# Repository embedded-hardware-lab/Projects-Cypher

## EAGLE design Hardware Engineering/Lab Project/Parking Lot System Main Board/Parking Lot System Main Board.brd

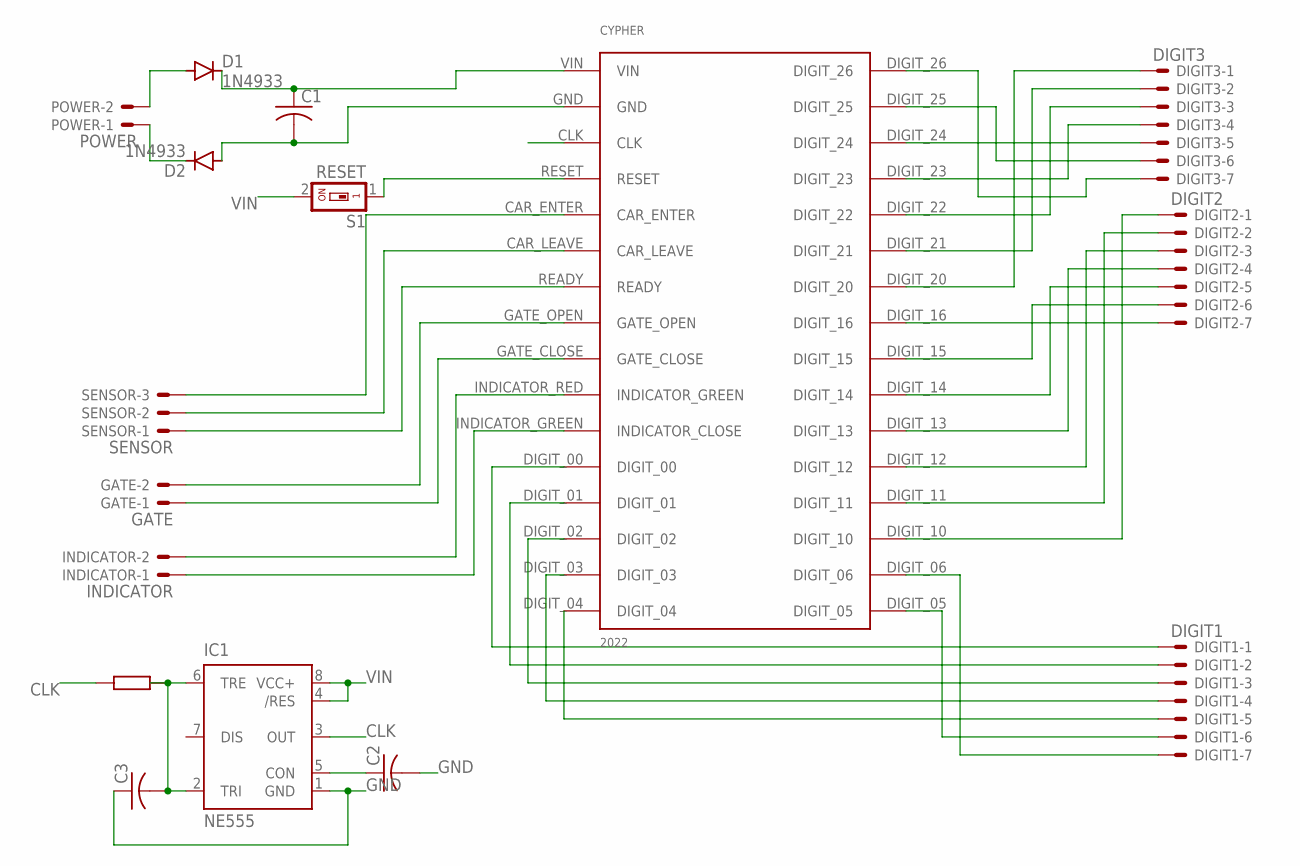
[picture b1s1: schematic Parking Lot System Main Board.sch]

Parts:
C1, C2, C3: C-US050-030X075; C050-030X075
CYPHER: CYPHER2022; CYPHER
D1, D2: 1N4933; DO41-10
DIGIT1: DIGIT1; 22-23-2071
DIGIT2: DIGIT2; 22-23-2071
DIGIT3: DIGIT3; 22-23-2071
GATE: GATE; 22-23-2021
IC1: NE555; DIL-08
INDICATOR: INDICATOR; 22-23-2021
POWER: POWER; 22-23-2021
S1: RESET; SMS-001
SENSOR: SENSOR; 22-23-2031

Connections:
CLK: CYPHER.CLK, IC1.3 (OUT); also elsewhere on the board
GND: C1.2, C2.2, C3.1, CYPHER.GND, D2.A, IC1.1 (GND); also elsewhere on the board
unnamed 2: CYPHER.CAR_ENTER, SENSOR.3; also elsewhere on the board
unnamed 3: CYPHER.RESET, S1.1; also elsewhere on the board
unnamed: D2.C, POWER.1
unnamed: D1.A, POWER.2
unnamed 6: CYPHER.CAR_LEAVE, SENSOR.2; also elsewhere on the board
unnamed 7: CYPHER.READY, SENSOR.1; also elsewhere on the board
unnamed: C3.2, IC1.2 (TRI), IC1.6 (TRE)
unnamed 9: CYPHER.GATE_OPEN, GATE.2; also elsewhere on the board
unnamed 10: CYPHER.GATE_CLOSE, GATE.1; also elsewhere on the board
unnamed 11: CYPHER.INDICATOR_RED (INDICATOR_GREEN), INDICATOR.2; also elsewhere on the board
unnamed: C2.1, IC1.5 (CON)
unnamed 13: CYPHER.INDICATOR_GREEN (INDICATOR_CLOSE), INDICATOR.1; also elsewhere on the board
unnamed 14: CYPHER.DIGIT_00, DIGIT1.1; also elsewhere on the board
unnamed 15: CYPHER.DIGIT_01, DIGIT1.2; also elsewhere on the board
unnamed 16: CYPHER.DIGIT_02, DIGIT1.3; also elsewhere on the board
unnamed 17: CYPHER.DIGIT_03, DIGIT1.4; also elsewhere on the board
unnamed 18: CYPHER.DIGIT_04, DIGIT1.5; also elsewhere on the board
unnamed 19: CYPHER.DIGIT_05, DIGIT1.6; also elsewhere on the board
unnamed 20: CYPHER.DIGIT_06, DIGIT1.7; also elsewhere on the board
unnamed 21: CYPHER.DIGIT_10, DIGIT2.1; also elsewhere on the board
unnamed 22: CYPHER.DIGIT_11, DIGIT2.2; also elsewhere on the board
unnamed 23: CYPHER.DIGIT_12, DIGIT2.3; also elsewhere on the board
unnamed 24: CYPHER.DIGIT_13, DIGIT2.4; also elsewhere on the board
unnamed 25: CYPHER.DIGIT_14, DIGIT2.5; also elsewhere on the board
unnamed 26: CYPHER.DIGIT_15, DIGIT2.6; also elsewhere on the board
unnamed 27: CYPHER.DIGIT_26, DIGIT3.7; also elsewhere on the board
unnamed 28: CYPHER.DIGIT_16, DIGIT2.7; also elsewhere on the board
unnamed 29: CYPHER.DIGIT_20, DIGIT3.1; also elsewhere on the board
unnamed 30: CYPHER.DIGIT_21, DIGIT3.2; also elsewhere on the board
unnamed 31: CYPHER.DIGIT_22, DIGIT3.3; also elsewhere on the board
unnamed 32: CYPHER.DIGIT_23, DIGIT3.4; also elsewhere on the board
unnamed 33: CYPHER.DIGIT_24, DIGIT3.5; also elsewhere on the board
unnamed 34: CYPHER.DIGIT_25, DIGIT3.6; also elsewhere on the board
VIN: C1.1, CYPHER.VIN, D1.C, IC1.4 (/RES), IC1.8 (VCC+), S1.2; also elsewhere on the board

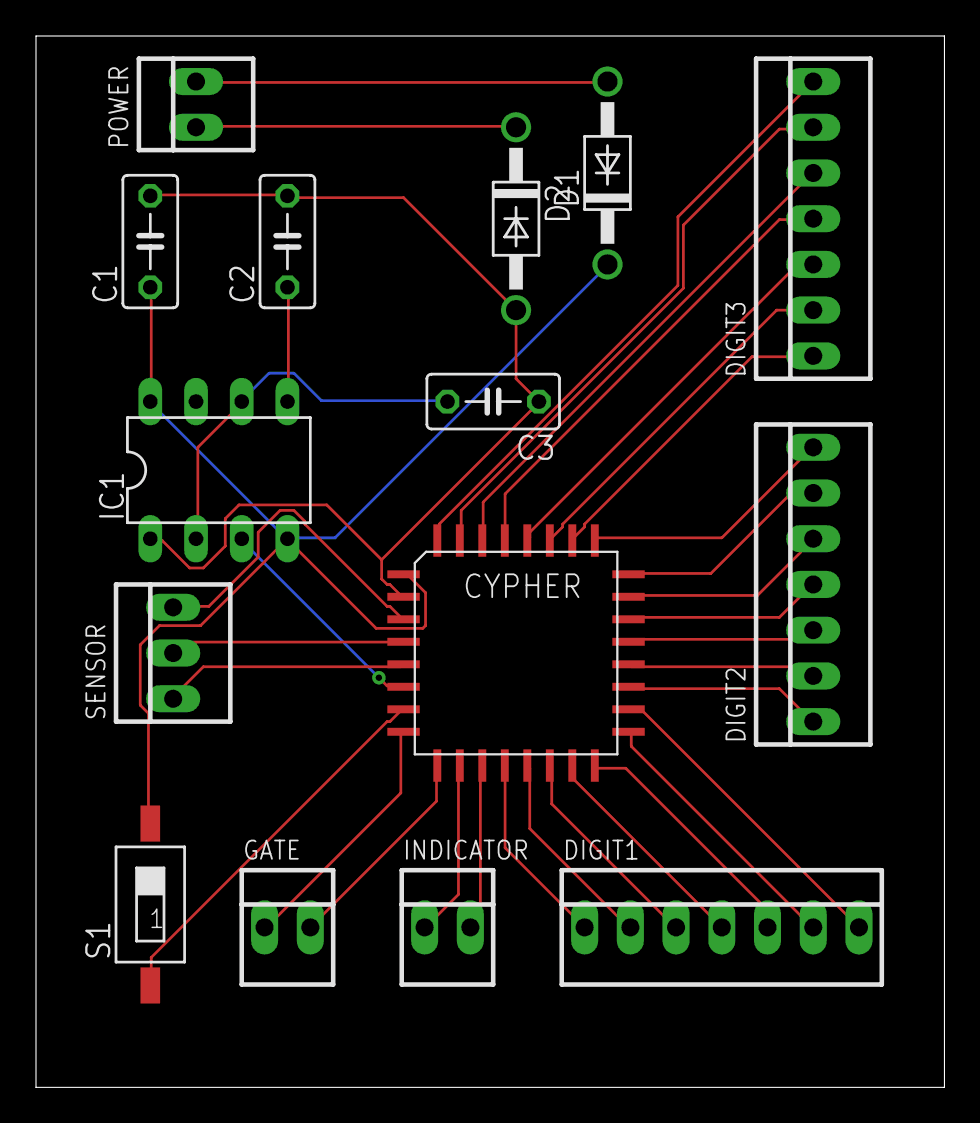
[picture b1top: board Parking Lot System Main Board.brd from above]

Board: 2 copper layers, 50.5 x 58.4 mm, 15 parts (0 on the bottom side), 36 nets.

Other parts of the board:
U$1: CYPHER2022; CYPHER

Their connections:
CLK: U$1.CLK; also elsewhere on the board
GND: U$1.GND; also elsewhere on the board
unnamed 2: U$1.CAR_ENTER; also elsewhere on the board
unnamed 3: U$1.RESET; also elsewhere on the board
unnamed 6: U$1.CAR_LEAVE; also elsewhere on the board
unnamed 7: U$1.READY; also elsewhere on the board
unnamed 9: U$1.GATE_OPEN; also elsewhere on the board
unnamed 10: U$1.GATE_CLOSE; also elsewhere on the board
unnamed 11: U$1.INDICATOR_RED; also elsewhere on the board
unnamed 13: U$1.INDICATOR_GREEN; also elsewhere on the board
unnamed 14: U$1.DIGIT_00; also elsewhere on the board
unnamed 15: U$1.DIGIT_01; also elsewhere on the board
unnamed 16: U$1.DIGIT_02; also elsewhere on the board
unnamed 17: U$1.DIGIT_03; also elsewhere on the board
unnamed 18: U$1.DIGIT_04; also elsewhere on the board
unnamed 19: U$1.DIGIT_05; also elsewhere on the board
unnamed 20: U$1.DIGIT_06; also elsewhere on the board
unnamed 21: U$1.DIGIT_10; also elsewhere on the board
unnamed 22: U$1.DIGIT_11; also elsewhere on the board
unnamed 23: U$1.DIGIT_12; also elsewhere on the board
unnamed 24: U$1.DIGIT_13; also elsewhere on the board
unnamed 25: U$1.DIGIT_14; also elsewhere on the board
unnamed 26: U$1.DIGIT_15; also elsewhere on the board
unnamed 27: U$1.DIGIT_26; also elsewhere on the board
unnamed 28: U$1.DIGIT_16; also elsewhere on the board
unnamed 29: U$1.DIGIT_20; also elsewhere on the board
unnamed 30: U$1.DIGIT_21; also elsewhere on the board
unnamed 31: U$1.DIGIT_22; also elsewhere on the board
unnamed 32: U$1.DIGIT_23; also elsewhere on the board
unnamed 33: U$1.DIGIT_24; also elsewhere on the board
unnamed 34: U$1.DIGIT_25; also elsewhere on the board
VIN: U$1.VIN; also elsewhere on the board

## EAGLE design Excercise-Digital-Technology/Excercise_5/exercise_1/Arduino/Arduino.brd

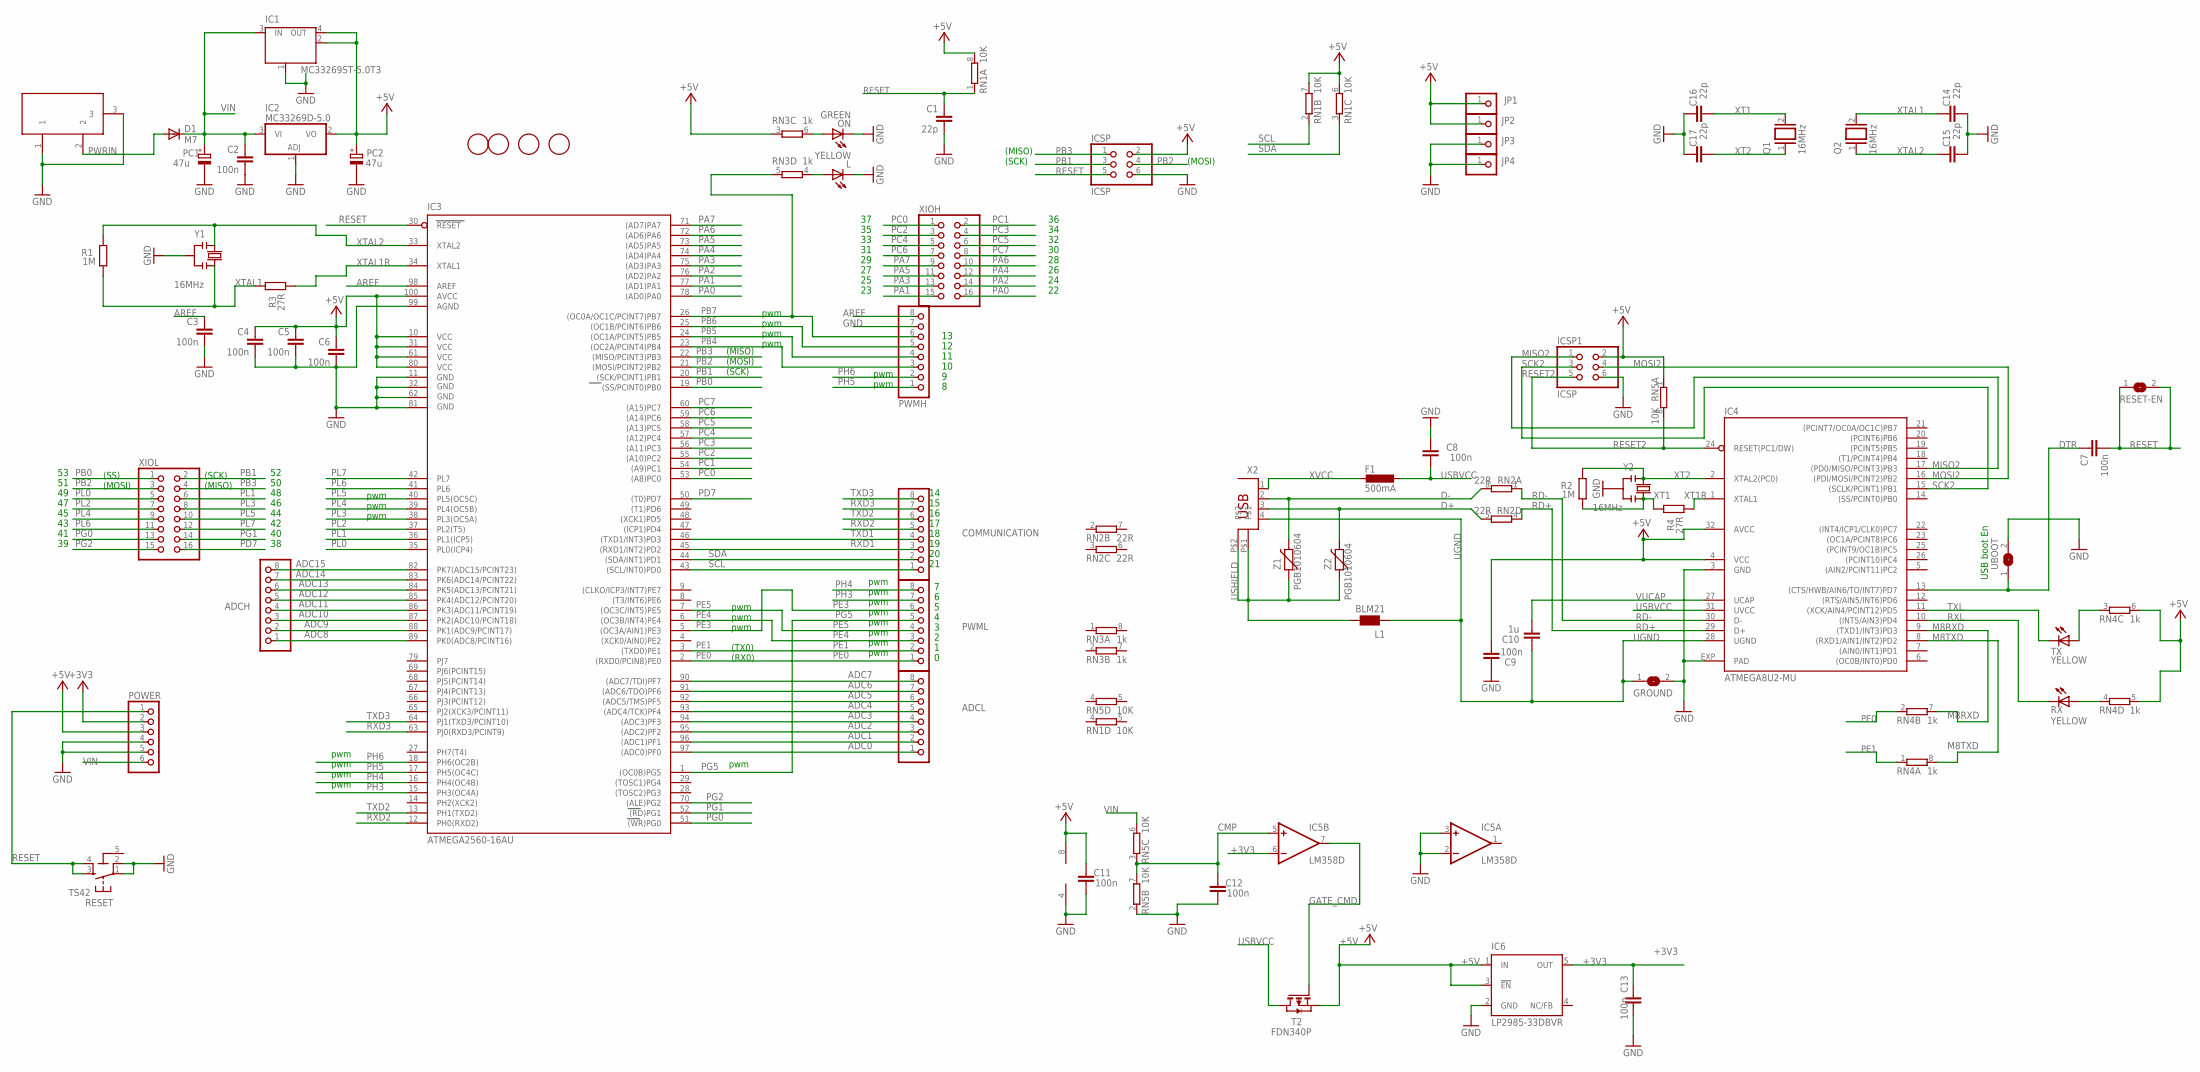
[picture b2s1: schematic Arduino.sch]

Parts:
ADCH: PINHD-1X8; 1X08
ADCL: PINHD-1X8; 1X08
C1, C14, C15, C16, C17: 22p; C0603-ROUND
C2, C3, C4, C5, C6, C7, C9, C12, C13: 100n; C0603-ROUND
C8, C11: 100n; C0603
C10: 1u; C0603-ROUND
COMMUNICATION: PINHD-1X8; 1X08
D1: M7; SMB
F1: 500mA; L1812
GROUND: SJ
IC1: MC33269ST-5.0T3; SOT223
IC2: MC33269D-5.0; DPACK
IC3: ATMEGA2560-16AU; TQFP100
IC4: ATMEGA8U2-MU; QFN32
IC5: LM358D; SO08
IC6: LP2985-33DBVR; SOT23-DBV
ICSP, ICSP1: ICSP; 2X03
JP1, JP2, JP3, JP4: PINHD-1X1; 1X01
L: YELLOW; CHIP-LED0805
L1: BLM21; 0805
ON: GREEN; CHIP-LED0805
PC1, PC2: 47u; PANASONIC_D
POWER: PINHD-1X6; 1X06
PWMH: PINHD-1X8; 1X08
PWML: PINHD-1X8; 1X08
Q1, Q2: 16MHz; QS
R1, R2: 1M; R0603-ROUND
R3, R4: 27R; R0603-ROUND
RESET: TS42
RESET-EN: SJ
RN1, RN5: 10K; CAT16
RN2: 22R; CAY16
RN3, RN4: 1k; CAY16
RX: YELLOW; CHIP-LED0805
T2: FDN340P; SOT-23
TX: YELLOW; CHIP-LED0805
U$2, U$3, U$4, U$5: FIDUCIALMOUNT; FIDUCIA-MOUNT
UBOOT: SJ
X1: DC21MMX; DC-21MM
X2: PN61729
XIOH: PINHD-2X8; 2X08
XIOL: PINHD-2X8; 2X08
Y1, Y2: 16MHz; RESONATOR
Z1, Z2: PGB1010604; CT/CN0603

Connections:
5-GND: RESET.5 (5-GND)
+3V3: C13.2, IC5.6 (-IN), IC6.5 (OUT), POWER.2
+5V: C4.1, C5.1, C6.1, C9.1, C11.2, IC1.2 (OUT), IC1.4 (OUT), IC2.2 (VO), IC3.10 (VCC), IC3.31 (VCC1), IC3.61 (VCC2), IC3.80 (VCC3), IC3.100 (AVCC), IC4.4 (VCC), IC4.32 (AVCC), IC5.8 (V+), IC6.1 (IN), IC6.3 (!EN), ICSP.2, ICSP1.2, JP1.1, JP2.1, PC2.+, POWER.3, RN1.6 (2), RN1.7 (2), RN1.8 (2), RN3.3 (1), RN4.5 (2), RN4.6 (2), RN5.1, T2.2 (S)
ADC0: ADCL.1, IC3.97 ((ADC0)PF0)
ADC1: ADCL.2, IC3.96 ((ADC1)PF1)
ADC2: ADCL.3, IC3.95 ((ADC2)PF2)
ADC3: ADCL.4, IC3.94 ((ADC3)PF3)
ADC4: ADCL.5, IC3.93 ((ADC4/TCK)PF4)
ADC5: ADCL.6, IC3.92 ((ADC5/TMS)PF5)
ADC6: ADCL.7, IC3.91 ((ADC6/TDO)PF6)
ADC7: ADCL.8, IC3.90 ((ADC7/TDI)PF7)
ADC8: ADCH.1, IC3.89 (PK0(ADC8/PCINT16))
ADC9: ADCH.2, IC3.88 (PK1(ADC9/PCINT17))
ADC10: ADCH.3, IC3.87 (PK2(ADC10/PCINT18))
ADC11: ADCH.4, IC3.86 (PK3(ADC11/PCINT19))
ADC12: ADCH.5, IC3.85 (PK4(ADC12/PCINT20))
ADC13: ADCH.6, IC3.84 (PK5(ADC13/PCINT21))
ADC14: ADCH.7, IC3.83 (PK6(ADC14/PCINT22))
ADC15: ADCH.8, IC3.82 (PK7(ADC15/PCINT23))
AREF: C3.1, IC3.98 (AREF), PWMH.8
CMP: C12.2, IC5.5 (+IN), RN5.3 (1), RN5.7 (2)
D+: RN2.5 (2), X2.3, Z2.2
D-: RN2.8 (2), X2.2, Z1.2
DTR: C7.1, IC4.13 ((CTS/HWB/AIN6/TO/INT7)PD7), UBOOT.1
GATE_CMD: IC5.7 (OUT), T2.3 (G)
GND: C1.2, C2.2, C3.2, C4.2, C5.2, C6.2, C8.2, C9.2, C11.1, C12.1, C13.1, C14.1, C15.1, C16.2, C17.2, GROUND.2, IC1.1 (GND/ADJ), IC2.1 (ADJ), IC3.11 (GND), IC3.32 (GND1), IC3.62 (GND2), IC3.81 (GND3), IC3.99 (AGND), IC4.3 (GND), IC4.EXP (PAD), IC5.2 (-IN), IC5.3 (+IN), IC5.4 (V-), IC6.2 (GND), ICSP.6, ICSP1.6, JP3.1, JP4.1, L.C, ON.C, PC1.-, PC2.-, POWER.4, POWER.5, PWMH.7, RESET.1, RESET.2, RN5.2 (1), UBOOT.2, X1.1, X1.3, Y1.2, Y2.2
M8RXD: IC4.9 ((TXD1/INT3)PD3), RN4.7 (2)
M8TXD: IC4.8 ((RXD1/AIN1/INT2)PD2), RN4.8 (2)
MISO2: IC4.17 ((PD0/MISO/PCINT3)PB3), ICSP1.1
MOSI2: IC4.16 ((PDI/MOSI/PCINT2)PB2), ICSP1.4
unnamed: L.A, RN3.4 (1)
unnamed: ON.A, RN3.6 (2)
unnamed: RN4.4 (1), RX.A
unnamed: RN4.3 (1), TX.A
PA0: IC3.78 ((AD0)PA0), XIOH.16
PA1: IC3.77 ((AD1)PA1), XIOH.15
PA2: IC3.76 ((AD2)PA2), XIOH.14
PA3: IC3.75 ((AD3)PA3), XIOH.13
PA4: IC3.74 ((AD4)PA4), XIOH.12
PA5: IC3.73 ((AD5)PA5), XIOH.11
PA6: IC3.72 ((AD6)PA6), XIOH.10
PA7: IC3.71 ((AD7)PA7), XIOH.9
PB0: IC3.19 ((SS/PCINT0)PB0), XIOL.1
PB1: IC3.20 ((SCK/PCINT1)PB1), ICSP.3, XIOL.2
PB2: IC3.21 ((MOSI/PCINT2)PB2), ICSP.4, XIOL.3
PB3: IC3.22 ((MISO/PCINT3)PB3), ICSP.1, XIOL.4
PB4: IC3.23 ((OC2A/PCINT4)PB4), PWMH.3
PB5: IC3.24 ((OC1A/PCINT5)PB5), PWMH.4
PB6: IC3.25 ((OC1B/PCINT6)PB6), PWMH.5
PB7: IC3.26 ((OC0A/OC1C/PCINT7)PB7), PWMH.6, RN3.5 (2)
PC0: IC3.53 ((A8)PC0), XIOH.1
PC1: IC3.54 ((A9)PC1), XIOH.2
PC2: IC3.55 ((A10)PC2), XIOH.3
PC3: IC3.56 ((A11)PC3), XIOH.4
PC4: IC3.57 ((A12)PC4), XIOH.5
PC5: IC3.58 ((A13)PC5), XIOH.6
PC6: IC3.59 ((A14)PC6), XIOH.7
PC7: IC3.60 ((A15)PC7), XIOH.8
PD7: IC3.50 ((T0)PD7), XIOL.16
PE0: IC3.2 ((RXD0/PCIN8)PE0), PWML.1, RN4.2 (1)
PE1: IC3.3 ((TXD0)PE1), PWML.2, RN4.1
PE3: IC3.5 ((OC3A/AIN1)PE3), PWML.6
PE4: IC3.6 ((OC3B/INT4)PE4), PWML.3
PE5: IC3.7 ((OC3C/INT5)PE5), PWML.4
PG0: IC3.51 ((WR)PG0), XIOL.13
PG1: IC3.52 ((RD)PG1), XIOL.14
PG2: IC3.70 ((ALE)PG2), XIOL.15
PG5: IC3.1 ((OC0B)PG5), PWML.5
PH3: IC3.15 (PH3(OC4A)), PWML.7
PH4: IC3.16 (PH4(OC4B)), PWML.8
PH5: IC3.17 (PH5(OC4C)), PWMH.1
PH6: IC3.18 (PH6(OC2B)), PWMH.2
PL0: IC3.35 (PL0(ICP4)), XIOL.5
PL1: IC3.36 (PL1(ICP5)), XIOL.6
PL2: IC3.37 (PL2(T5)), XIOL.7
PL3: IC3.38 (PL3(OC5A)), XIOL.8
PL4: IC3.39 (PL4(OC5B)), XIOL.9
PL5: IC3.40 (PL5(OC5C)), XIOL.10
PL6: IC3.41 (PL6), XIOL.11
PL7: IC3.42 (PL7), XIOL.12
PWRIN: D1.A, X1.2
RD+: IC4.29 (D+), RN2.4 (1)
RD-: IC4.30 (D-), RN2.1
RESET: C1.1, C7.2, IC3.30 (RESET), ICSP.5, POWER.1, RESET.3, RESET.4, RESET-EN.1, RESET-EN.2, RN1.1
RESET2: IC4.24 (RESET(PC1/DW)), ICSP1.5, RN5.8 (2)
RXD1: COMMUNICATION.3, IC3.45 ((RXD1/INT2)PD2)
RXD2: COMMUNICATION.5, IC3.12 (PH0(RXD2))
RXD3: COMMUNICATION.7, IC3.63 (PJ0(RXD3/PCINT9))
RXL: IC4.10 ((INT5/AIN3)PD4), RX.C
SCK2: IC4.15 ((SCLK/PCINT1)PB1), ICSP1.3
SCL: COMMUNICATION.1, IC3.43 ((SCL/INT0)PD0), RN1.2 (1)
SDA: COMMUNICATION.2, IC3.44 ((SDA/INT1)PD1), RN1.3 (1)
TXD1: COMMUNICATION.4, IC3.46 ((TXD1/INT3)PD3)
TXD2: COMMUNICATION.6, IC3.13 (PH1(TXD2))
TXD3: COMMUNICATION.8, IC3.64 (PJ1(TXD3/PCINT10))
TXL: IC4.11 ((XCK/AIN4/PCINT12)PD5), TX.C
UGND: C10.2, GROUND.1, IC4.28 (UGND), L1.1, X2.4
USBVCC: C8.1, F1.1, IC4.31 (UVCC), T2.1 (D)
USHIELD: L1.2, X2.P$1, X2.P$2, Z1.1, Z2.1
VIN: C2.1, D1.C, IC1.3 (IN), IC2.3 (VI), PC1.+, POWER.6, RN5.6 (2)
VUCAP: C10.1, IC4.27 (UCAP)
XT1: C16.1, Q1.2, R2.1, R4.2, Y2.3
XT1R: IC4.1 (XTAL1), R4.1
XT2: C17.1, IC4.2 (XTAL2(PC0)), Q1.1, R2.2, Y2.1
XTAL1: C14.2, Q2.2, R1.1, R3.2, Y1.3
XTAL1R: IC3.34 (XTAL1), R3.1
XTAL2: C15.2, IC3.33 (XTAL2), Q2.1, R1.2, Y1.1
XVCC: F1.2, X2.1

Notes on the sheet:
(SCK)
(MISO)
(MOSI)
pwm
(TX0)
(RX0)
(SS)
USB boot En

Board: 2 copper layers, 72 parts (0 on the bottom side), 107 nets, no tracks yet.

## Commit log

2022-05-15 change
2022-05-15 add diagrams
2022-05-15 add changes
2022-05-15 add system architecture
2022-05-25 rearrange
2022-06-02 update vhdl
2022-06-08 Update transcript
2022-06-08 ignore
2022-06-08 update dir
2022-06-08 intermediate
2022-06-12 upload
2022-06-12 integrate
2022-06-14 kasitau
2022-06-17 init
2022-06-18 updatae
2022-06-18 uoadte
2022-06-18 5tgt4
2022-06-18 gretr
2022-06-18 sagser
2022-06-18 vbcv
2022-06-18 jhgu
2022-06-19 delete
2022-06-20 dsfds
2022-06-20 gfdd
2022-06-20 dsaasd
2022-06-20 dfdzf
2022-06-28 presenttaion
